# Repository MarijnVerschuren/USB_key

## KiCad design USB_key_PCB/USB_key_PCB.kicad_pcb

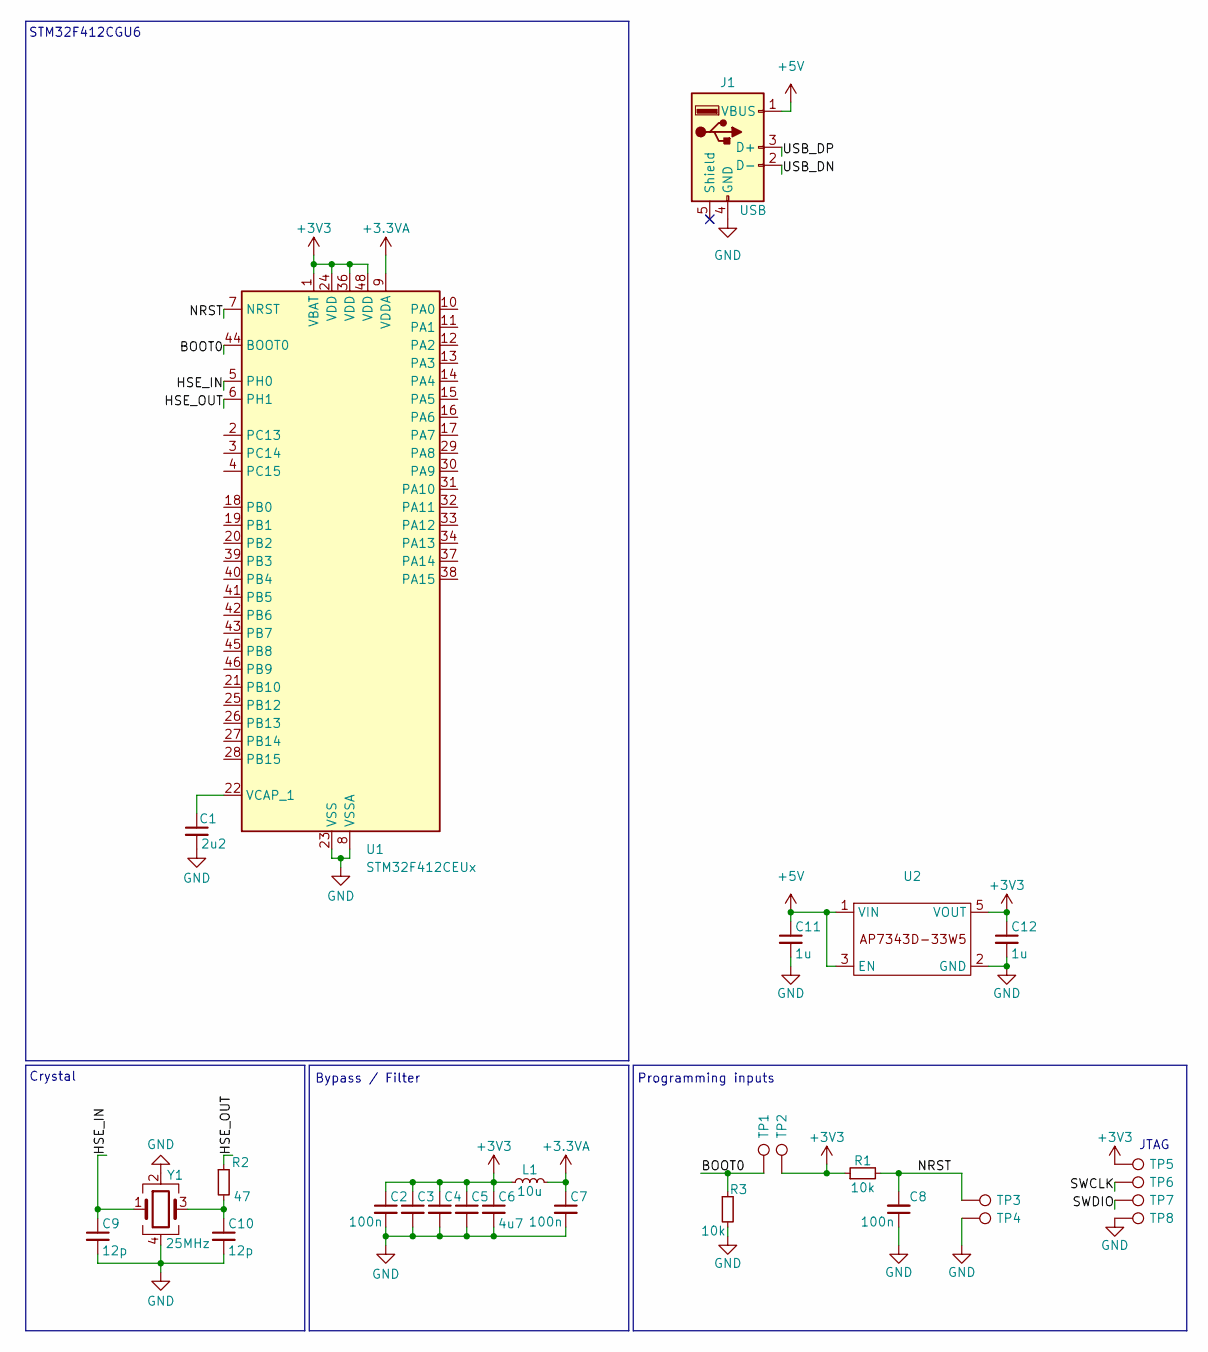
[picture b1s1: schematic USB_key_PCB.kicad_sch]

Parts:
C1: 2u2; C_0402_1005Metric; LCSC C12530
C2, C3, C4, C5, C7, C8: 100n; C_0402_1005Metric
C6: 4u7; C_0402_1005Metric
C9, C10: 12p; C_0402_1005Metric
C11, C12: 1u; C_0402_1005Metric
J1: USB; PCB_USB
L1: 10u; L_0402_1005Metric
R1, R3: 10k; R_0402_1005Metric
R2: 47; R_0402_1005Metric; LCSC C25118
TP1, TP2, TP3, TP4, TP5, TP6, TP7, TP8: TestPoint_Pad_D1.0mm
U1: STM32F412CEUx; QFN-48-1EP_7x7mm_P0.5mm_EP5.6x5.6mm
U2: X2-DFN1010-4
Y1: 25MHz; Crystal_SMD_3225-4Pin_3.2x2.5mm

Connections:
+3.3VA: C7.1, L1.2, U1.9 (VDDA)
+3V3: C2.1, C3.1, C4.1, C5.1, C6.1, C12.1, L1.1, R1.1, TP2.1, TP5.1, U1.1 (VBAT), U1.24 (VDD), U1.36 (VDD), U1.48 (VDD), U2.5 (VOUT)
+5V: C11.1, J1.1 (VBUS), U2.1 (VIN), U2.3 (EN)
/BOOT0: R3.1, TP1.1, U1.44 (BOOT0)
/HSE_IN: C9.1, U1.5 (PH0), Y1.1
/HSE_OUT: R2.1, U1.6 (PH1)
/NRST: C8.2, R1.2, TP3.1, U1.7 (NRST)
/SWCLK: TP6.1
/SWDIO: TP7.1
/USB_DN: J1.2 (D-)
/USB_DP: J1.3 (D+)
GND: C1.2, C2.2, C3.2, C4.2, C5.2, C6.2, C7.2, C8.1, C9.2, C10.2, C11.2, C12.2, J1.4 (GND), R3.2, TP4.1, TP8.1, U1.8 (VSSA), U1.23 (VSS), U1.35 (VSS), U1.47 (VSS), U1.49 (VSS), U2.2 (GND), Y1.2, Y1.4
unnamed: C10.1, R2.2, Y1.3
unnamed: C1.1, U1.22 (VCAP_1)

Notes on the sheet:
STM32F412CGU6
Bypass / Filter
Programming inputs
Crystal
JTAG

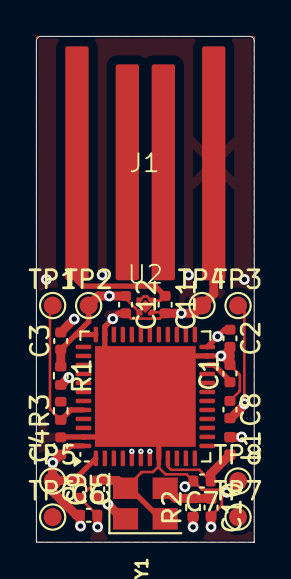
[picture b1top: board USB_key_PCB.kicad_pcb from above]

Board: 4 copper layers, 12.1 x 28.1 mm, 28 parts (0 on the bottom side), 10 nets.

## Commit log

2024-06-07 USB connector
2024-06-07 Layout start
